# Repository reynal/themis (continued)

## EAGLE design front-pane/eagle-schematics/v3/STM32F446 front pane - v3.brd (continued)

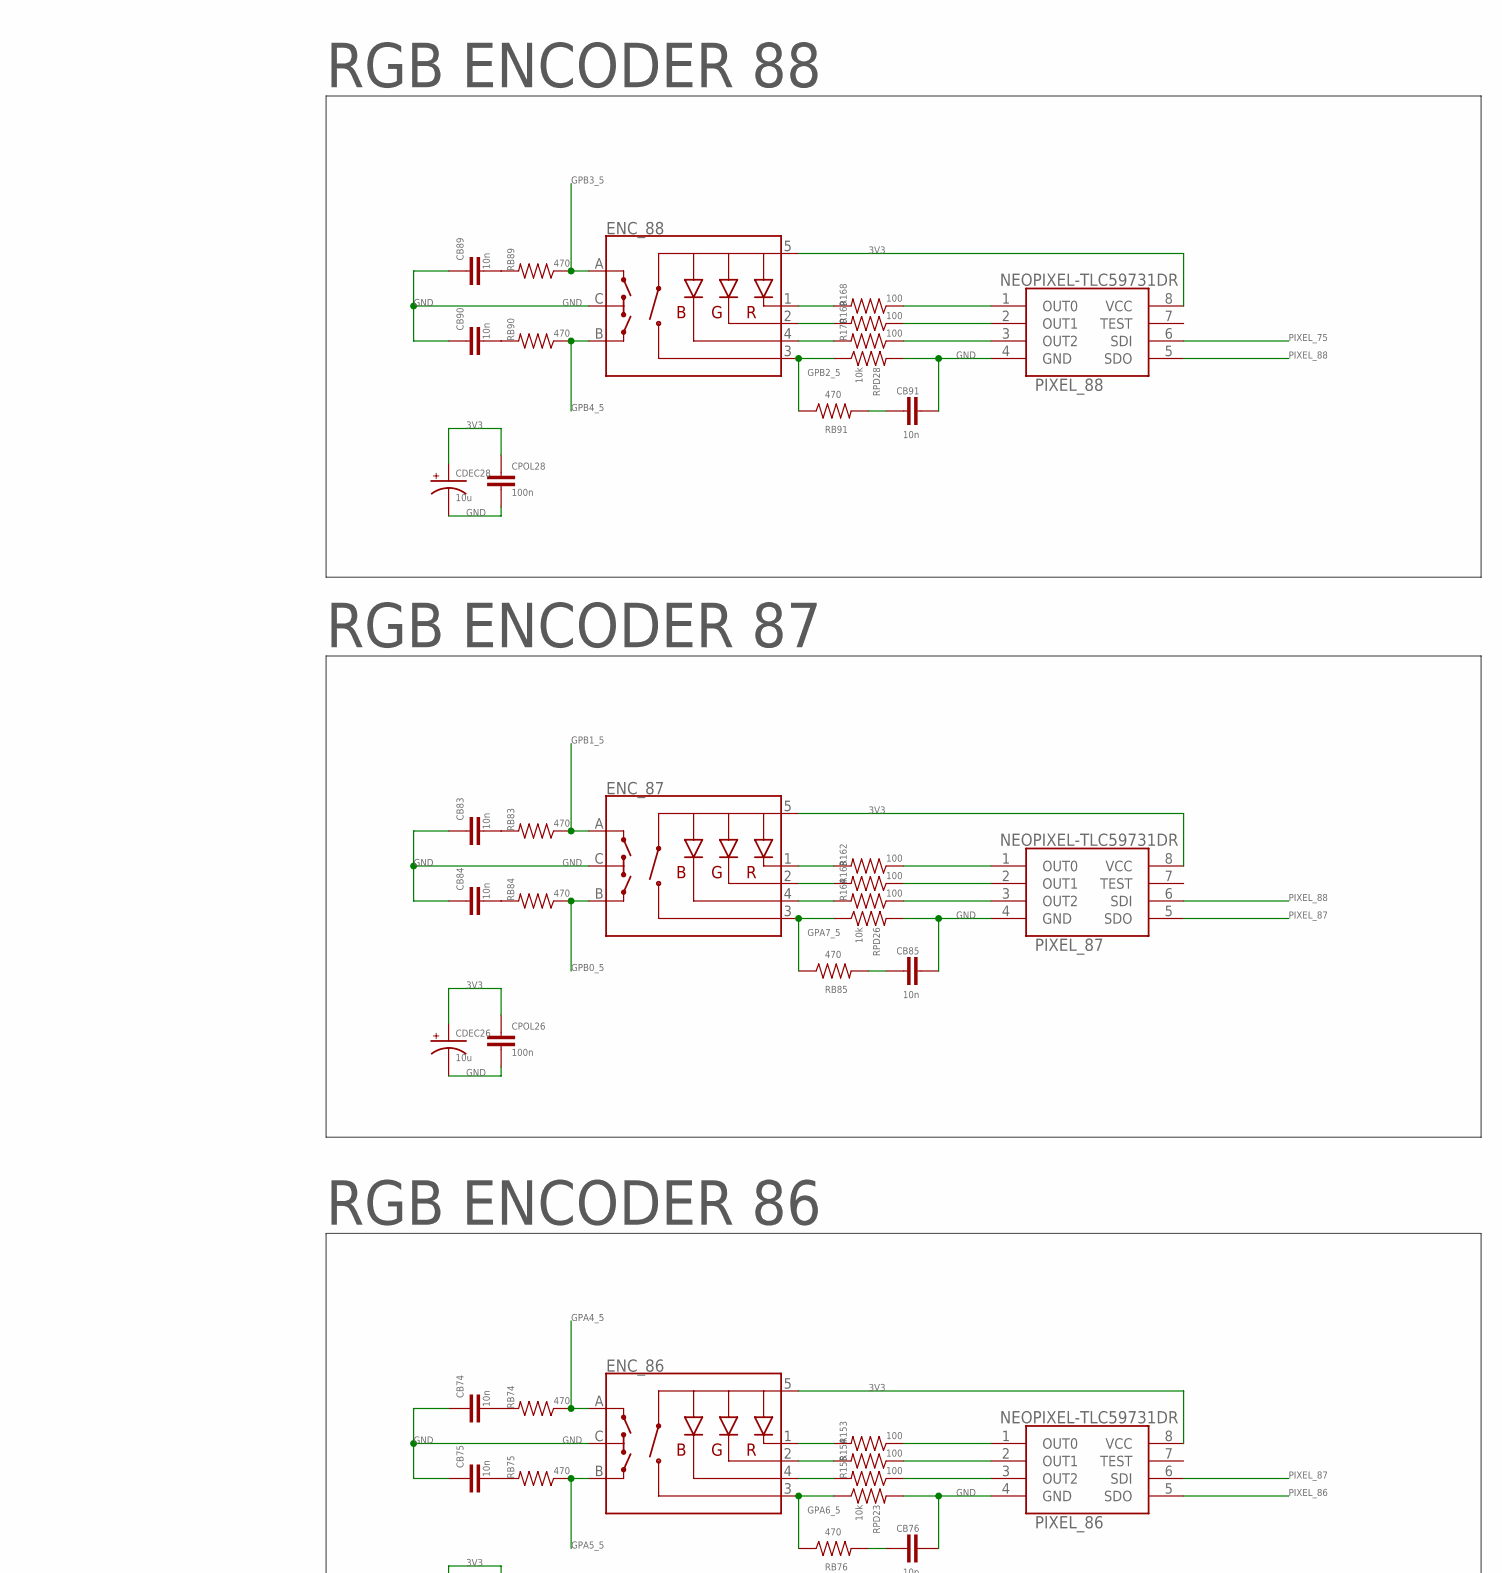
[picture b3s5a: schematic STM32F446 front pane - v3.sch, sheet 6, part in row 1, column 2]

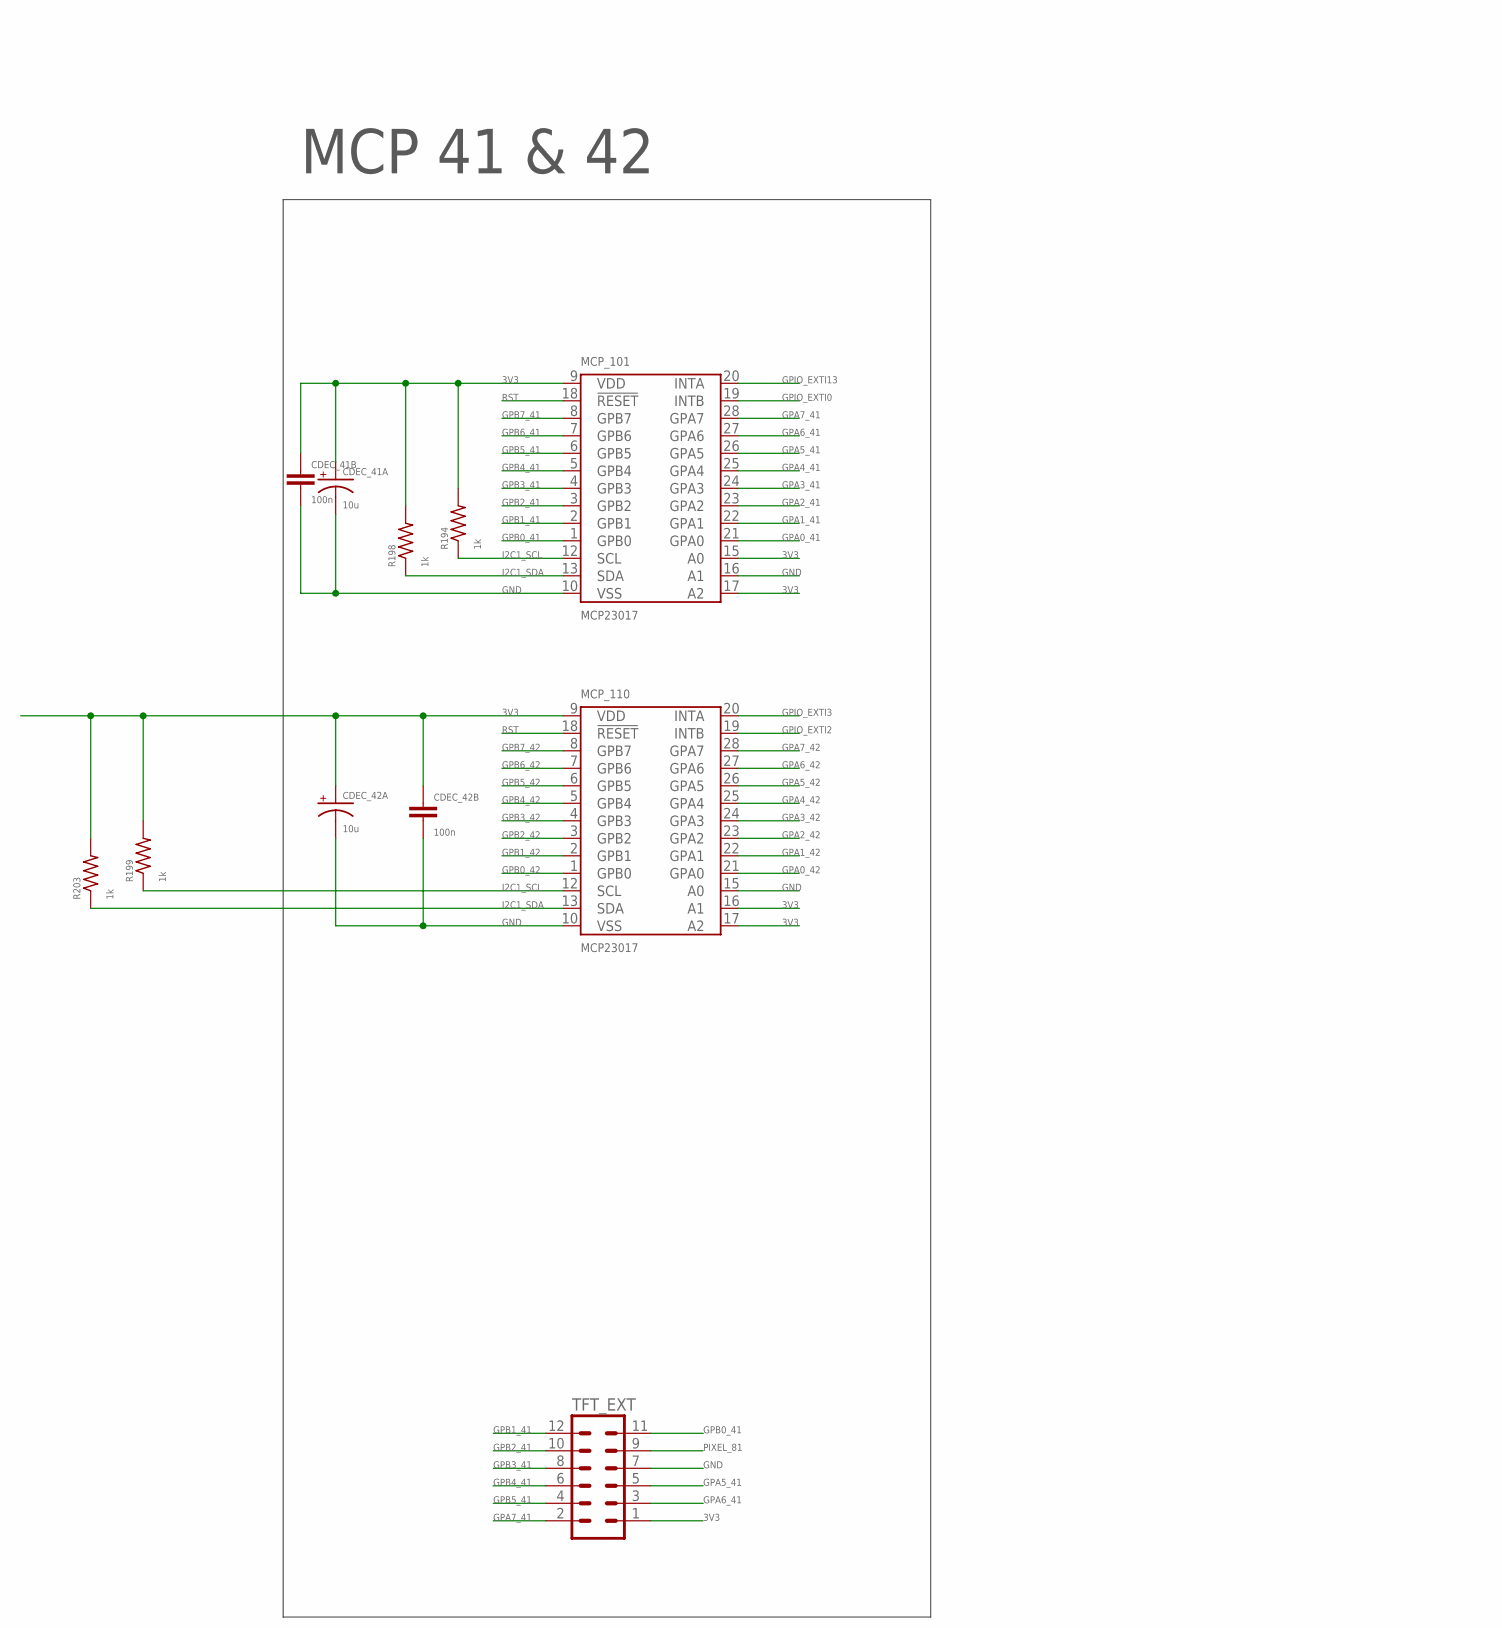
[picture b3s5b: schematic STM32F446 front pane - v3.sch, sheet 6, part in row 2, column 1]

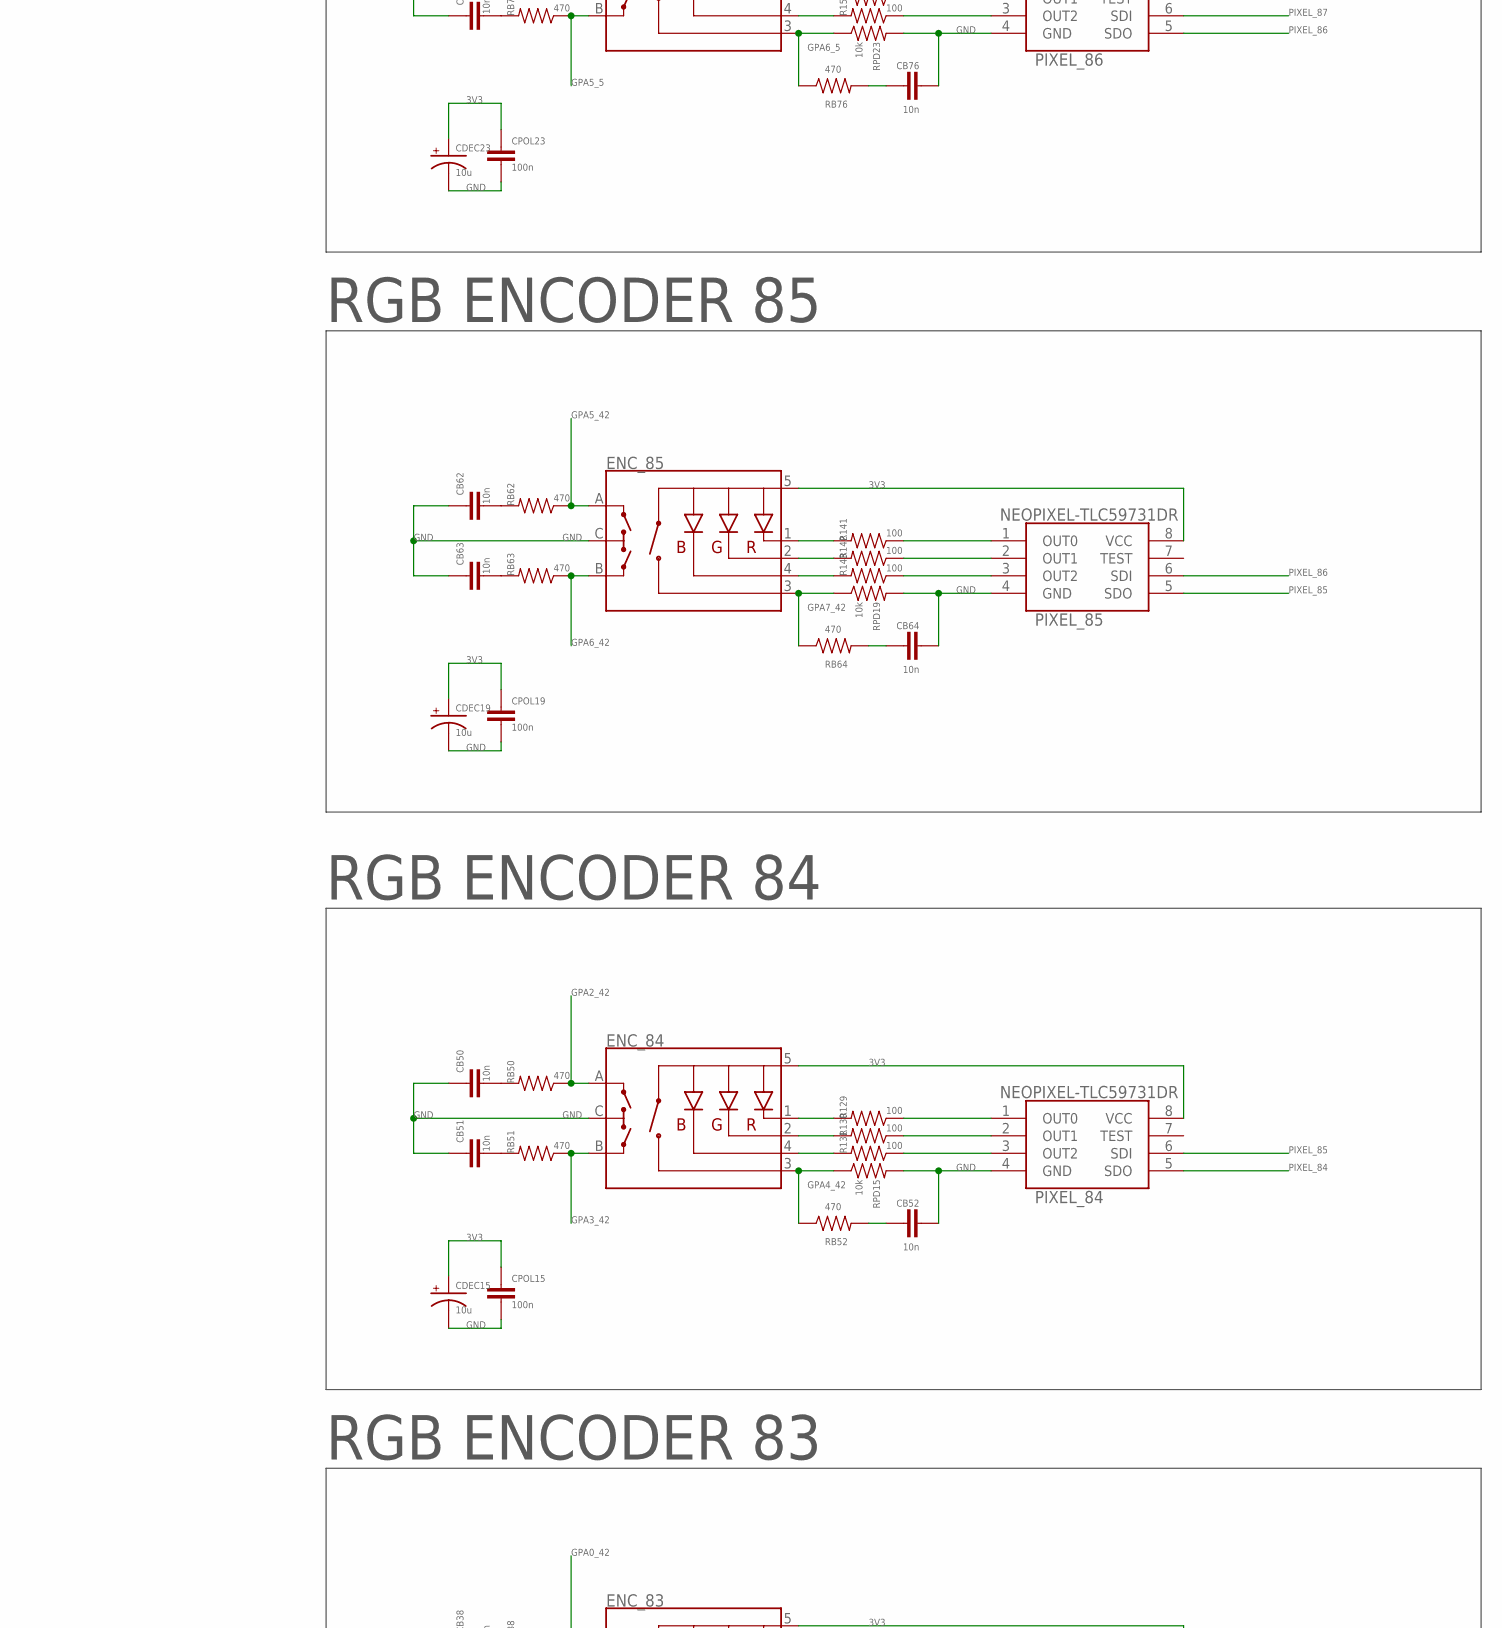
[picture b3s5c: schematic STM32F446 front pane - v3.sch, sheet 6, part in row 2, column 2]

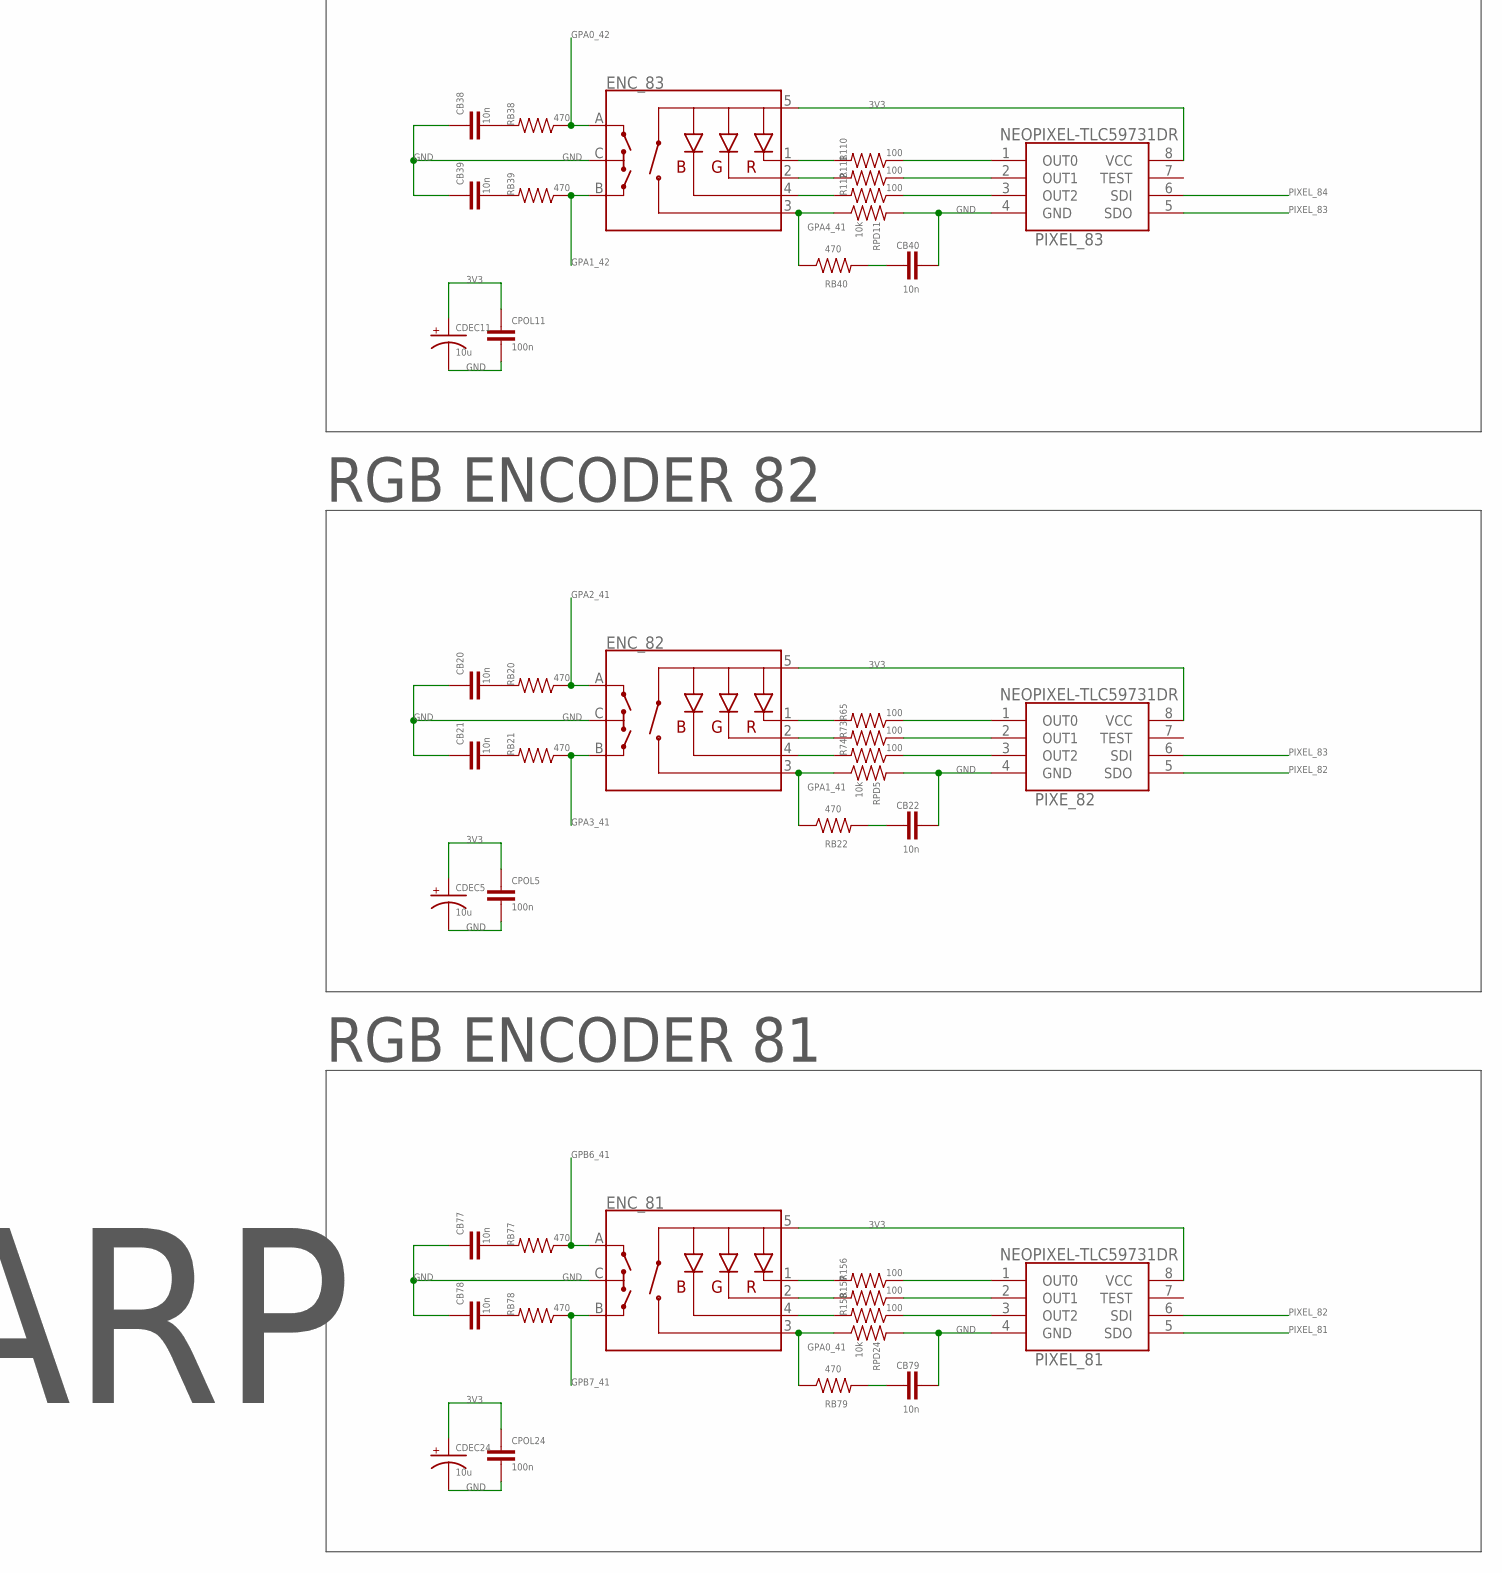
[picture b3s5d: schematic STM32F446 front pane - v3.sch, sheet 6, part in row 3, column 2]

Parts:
CB20, CB21, CB22, CB38, CB39, CB40, CB50, CB51, CB52, CB62, CB63, CB64, CB74, CB75, CB76, CB77, CB78, CB79, CB83, CB84, CB85, CB89, CB90, CB91: 10n; 0805-CAP
CDEC5, CDEC11, CDEC15, CDEC19, CDEC23, CDEC24, CDEC26, CDEC28: 10u; CPOL2917
CDEC_41A, CDEC_42A: 10u; CPOL2917
CDEC_41B, CDEC_42B: 100n; 0805-CAP
CPOL5, CPOL11, CPOL15, CPOL19, CPOL23, CPOL24, CPOL26, CPOL28: 100n; 0805-CAP
ENC_81, ENC_82, ENC_83, ENC_84, ENC_85, ENC_86, ENC_87, ENC_88: ENCODER-RGB-SWITCH-NO_NUT; ENCODER_LED_3
MCP_101, MCP_110: MCP23017; SOIC-28
PIXEL_81, PIXEL_83, PIXEL_84, PIXEL_85, PIXEL_86, PIXEL_87, PIXEL_88: NEOPIXEL-TLC59731DR; SOIC127P600X175-8N
PIXE_82: NEOPIXEL-TLC59731DR; SOIC127P600X175-8N
R65, R73, R74, R110, R111, R112, R129, R130, R131, R141, R142, R143, R153, R154, R155, R156, R157, R158, R162, R163, R164, R168, R169, R170: 100; 1206
R194, R198, R199, R203: 1k; R0805
RB20, RB21, RB22, RB38, RB39, RB40, RB50, RB51, RB52, RB62, RB63, RB64, RB74, RB75, RB76, RB77, RB78, RB79, RB83, RB84, RB85, RB89, RB90, RB91: 470; 1206
RPD5, RPD11, RPD15, RPD19, RPD23, RPD24, RPD26, RPD28: 10k; 1206
TFT_EXT: MA06-2

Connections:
3V3: CDEC5.+, CDEC11.+, CDEC15.+, CDEC19.+, CDEC23.+, CDEC24.+, CDEC26.+, CDEC28.+, CDEC_41A.+, CDEC_41B.1, CDEC_42A.+, CDEC_42B.1, CPOL5.1, CPOL11.1, CPOL15.1, CPOL19.1, CPOL23.1, CPOL24.1, CPOL26.1, CPOL28.1, ENC_81.5 (+), ENC_82.5 (+), ENC_83.5 (+), ENC_84.5 (+), ENC_85.5 (+), ENC_86.5 (+), ENC_87.5 (+), ENC_88.5 (+), MCP_101.9 (VDD), MCP_101.15 (A0), MCP_101.17 (A2), MCP_110.9 (VDD), MCP_110.16 (A1), MCP_110.17 (A2), PIXEL_81.8 (VCC), PIXEL_83.8 (VCC), PIXEL_84.8 (VCC), PIXEL_85.8 (VCC), PIXEL_86.8 (VCC), PIXEL_87.8 (VCC), PIXEL_88.8 (VCC), PIXE_82.8 (VCC), R194.2, R198.2, R199.2, R203.2, TFT_EXT.1; also elsewhere on the board
GND: CB20.1, CB21.1, CB22.2, CB38.1, CB39.1, CB40.2, CB50.1, CB51.1, CB52.2, CB62.1, CB63.1, CB64.2, CB74.1, CB75.1, CB76.2, CB77.1, CB78.1, CB79.2, CB83.1, CB84.1, CB85.2, CB89.1, CB90.1, CB91.2, CDEC5.-, CDEC11.-, CDEC15.-, CDEC19.-, CDEC23.-, CDEC24.-, CDEC26.-, CDEC28.-, CDEC_41A.-, CDEC_41B.2, CDEC_42A.-, CDEC_42B.2, CPOL5.2, CPOL11.2, CPOL15.2, CPOL19.2, CPOL23.2, CPOL24.2, CPOL26.2, CPOL28.2, ENC_81.C, ENC_82.C, ENC_83.C, ENC_84.C, ENC_85.C, ENC_86.C, ENC_87.C, ENC_88.C, MCP_101.10 (VSS), MCP_101.16 (A1), MCP_110.10 (VSS), MCP_110.15 (A0), PIXEL_81.4 (GND), PIXEL_83.4 (GND), PIXEL_84.4 (GND), PIXEL_85.4 (GND), PIXEL_86.4 (GND), PIXEL_87.4 (GND), PIXEL_88.4 (GND), PIXE_82.4 (GND), RPD5.2, RPD11.2, RPD15.2, RPD19.2, RPD23.2, RPD24.2, RPD26.2, RPD28.2, TFT_EXT.7; also elsewhere on the board
GPA0_41: ENC_81.3 (SW), MCP_101.21 (GPA0), RB79.1, RPD24.1
GPA0_42: ENC_83.A, MCP_110.21 (GPA0), RB38.1
GPA1_41: ENC_82.3 (SW), MCP_101.22 (GPA1), RB22.1, RPD5.1
GPA1_42: ENC_83.B, MCP_110.22 (GPA1), RB39.1
GPA2_41: ENC_82.A, MCP_101.23 (GPA2), RB20.1
GPA2_42: ENC_84.A, MCP_110.23 (GPA2), RB50.1
GPA3_41: ENC_82.B, MCP_101.24 (GPA3), RB21.1
GPA3_42: ENC_84.B, MCP_110.24 (GPA3), RB51.1
GPA4_5: ENC_86.A, RB74.1; also elsewhere on the board
GPA4_41: ENC_83.3 (SW), MCP_101.25 (GPA4), RB40.1, RPD11.1
GPA4_42: ENC_84.3 (SW), MCP_110.25 (GPA4), RB52.1, RPD15.1
GPA5_5: ENC_86.B, RB75.1; also elsewhere on the board
GPA5_41: MCP_101.26 (GPA5), TFT_EXT.5
GPA5_42: ENC_85.A, MCP_110.26 (GPA5), RB62.1
GPA6_5: ENC_86.3 (SW), RB76.1, RPD23.1; also elsewhere on the board
GPA6_41: MCP_101.27 (GPA6), TFT_EXT.3
GPA6_42: ENC_85.B, MCP_110.27 (GPA6), RB63.1
GPA7_5: ENC_87.3 (SW), RB85.1, RPD26.1; also elsewhere on the board
GPA7_41: MCP_101.28 (GPA7), TFT_EXT.2
GPA7_42: ENC_85.3 (SW), MCP_110.28 (GPA7), RB64.1, RPD19.1
GPB0_5: ENC_87.B, RB84.1; also elsewhere on the board
GPB0_41: MCP_101.1 (GPB0), TFT_EXT.11
GPB0_42: MCP_110.1 (GPB0); also elsewhere on the board
GPB1_5: ENC_87.A, RB83.1; also elsewhere on the board
GPB1_41: MCP_101.2 (GPB1), TFT_EXT.12
GPB1_42: MCP_110.2 (GPB1); also elsewhere on the board
GPB2_5: ENC_88.3 (SW), RB91.1, RPD28.1; also elsewhere on the board
GPB2_41: MCP_101.3 (GPB2), TFT_EXT.10
GPB2_42: MCP_110.3 (GPB2); also elsewhere on the board
GPB3_5: ENC_88.A, RB89.1; also elsewhere on the board
GPB3_41: MCP_101.4 (GPB3), TFT_EXT.8
GPB3_42: MCP_110.4 (GPB3); also elsewhere on the board
GPB4_5: ENC_88.B, RB90.1; also elsewhere on the board
GPB4_41: MCP_101.5 (GPB4), TFT_EXT.6
GPB4_42: MCP_110.5 (GPB4); also elsewhere on the board
GPB5_41: MCP_101.6 (GPB5), TFT_EXT.4
GPB5_42: MCP_110.6 (GPB5); also elsewhere on the board
GPB6_41: ENC_81.A, MCP_101.7 (GPB6), RB77.1
GPB6_42: MCP_110.7 (GPB6); also elsewhere on the board
GPB7_41: ENC_81.B, MCP_101.8 (GPB7), RB78.1
GPB7_42: MCP_110.8 (GPB7); also elsewhere on the board
GPIO_EXTI0: MCP_101.19 (INTB); also elsewhere on the board
GPIO_EXTI2: MCP_110.19 (INTB); also elsewhere on the board
GPIO_EXTI3: MCP_110.20 (INTA); also elsewhere on the board
GPIO_EXTI13: MCP_101.20 (INTA); also elsewhere on the board
I2C1_SCL: MCP_101.12 (SCL), MCP_110.12 (SCL), R194.1, R199.1; also elsewhere on the board
I2C1_SDA: MCP_101.13 (SDA), MCP_110.13 (SDA), R198.1, R203.1; also elsewhere on the board
unnamed: ENC_82.1 (-R), R65.2
unnamed: ENC_82.2 (-G), R73.2
unnamed: ENC_82.4 (-B), R74.2
unnamed: PIXE_82.1 (OUT0), R65.1
unnamed: PIXE_82.2 (OUT1), R73.1
unnamed: PIXE_82.3 (OUT2), R74.1
unnamed: CB20.2, RB20.2
unnamed: CB21.2, RB21.2
unnamed: CB22.1, RB22.2
unnamed: ENC_83.1 (-R), R110.2
unnamed: ENC_83.2 (-G), R111.2
unnamed: ENC_83.4 (-B), R112.2
unnamed: PIXEL_83.1 (OUT0), R110.1
unnamed: PIXEL_83.2 (OUT1), R111.1
unnamed: PIXEL_83.3 (OUT2), R112.1
unnamed: CB38.2, RB38.2
unnamed: CB39.2, RB39.2
unnamed: CB40.1, RB40.2
unnamed: ENC_84.1 (-R), R129.2
unnamed: ENC_84.2 (-G), R130.2
unnamed: ENC_84.4 (-B), R131.2
unnamed: PIXEL_84.1 (OUT0), R129.1
unnamed: PIXEL_84.2 (OUT1), R130.1
unnamed: PIXEL_84.3 (OUT2), R131.1
unnamed: CB50.2, RB50.2
unnamed: CB51.2, RB51.2
unnamed: CB52.1, RB52.2
unnamed: ENC_85.1 (-R), R141.2
unnamed: ENC_85.2 (-G), R142.2
unnamed: ENC_85.4 (-B), R143.2
unnamed: PIXEL_85.1 (OUT0), R141.1
unnamed: PIXEL_85.2 (OUT1), R142.1
unnamed: PIXEL_85.3 (OUT2), R143.1
unnamed: CB62.2, RB62.2
unnamed: CB63.2, RB63.2
unnamed: CB64.1, RB64.2
unnamed: ENC_86.1 (-R), R153.2
unnamed: ENC_86.2 (-G), R154.2
unnamed: ENC_86.4 (-B), R155.2
unnamed: PIXEL_86.1 (OUT0), R153.1
unnamed: PIXEL_86.2 (OUT1), R154.1
unnamed: PIXEL_86.3 (OUT2), R155.1
unnamed: CB74.2, RB74.2
unnamed: CB75.2, RB75.2
unnamed: CB76.1, RB76.2
unnamed: ENC_81.1 (-R), R156.2
unnamed: ENC_81.2 (-G), R157.2
unnamed: ENC_81.4 (-B), R158.2
unnamed: PIXEL_81.1 (OUT0), R156.1
unnamed: PIXEL_81.2 (OUT1), R157.1
unnamed: PIXEL_81.3 (OUT2), R158.1
unnamed: CB77.2, RB77.2
unnamed: CB78.2, RB78.2
unnamed: CB79.1, RB79.2
unnamed: ENC_87.1 (-R), R162.2
unnamed: ENC_87.2 (-G), R163.2
unnamed: ENC_87.4 (-B), R164.2
unnamed: PIXEL_87.1 (OUT0), R162.1
unnamed: PIXEL_87.2 (OUT1), R163.1
unnamed: PIXEL_87.3 (OUT2), R164.1
unnamed: CB83.2, RB83.2
unnamed: CB84.2, RB84.2
unnamed: CB85.1, RB85.2
unnamed: ENC_88.1 (-R), R168.2
unnamed: ENC_88.2 (-G), R169.2
unnamed: ENC_88.4 (-B), R170.2
unnamed: PIXEL_88.1 (OUT0), R168.1
unnamed: PIXEL_88.2 (OUT1), R169.1
unnamed: PIXEL_88.3 (OUT2), R170.1
unnamed: CB89.2, RB89.2
unnamed: CB90.2, RB90.2
unnamed: CB91.1, RB91.2
PIXEL_75: PIXEL_88.6 (SDI); also elsewhere on the board
PIXEL_81: PIXEL_81.5 (SDO), TFT_EXT.9
PIXEL_82: PIXEL_81.6 (SDI), PIXE_82.5 (SDO)
PIXEL_83: PIXEL_83.5 (SDO), PIXE_82.6 (SDI)
PIXEL_84: PIXEL_83.6 (SDI), PIXEL_84.5 (SDO)
PIXEL_85: PIXEL_84.6 (SDI), PIXEL_85.5 (SDO)
PIXEL_86: PIXEL_85.6 (SDI), PIXEL_86.5 (SDO)
PIXEL_87: PIXEL_86.6 (SDI), PIXEL_87.5 (SDO)
PIXEL_88: PIXEL_87.6 (SDI), PIXEL_88.5 (SDO)
RST: MCP_101.18 (!RESET), MCP_110.18 (!RESET); also elsewhere on the board

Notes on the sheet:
ARP
RGB ENCODER 81
RGB ENCODER 82
RGB ENCODER 83
RGB ENCODER 84
RGB ENCODER 85
RGB ENCODER 86
RGB ENCODER 87
RGB ENCODER 88
MCP 41 & 42

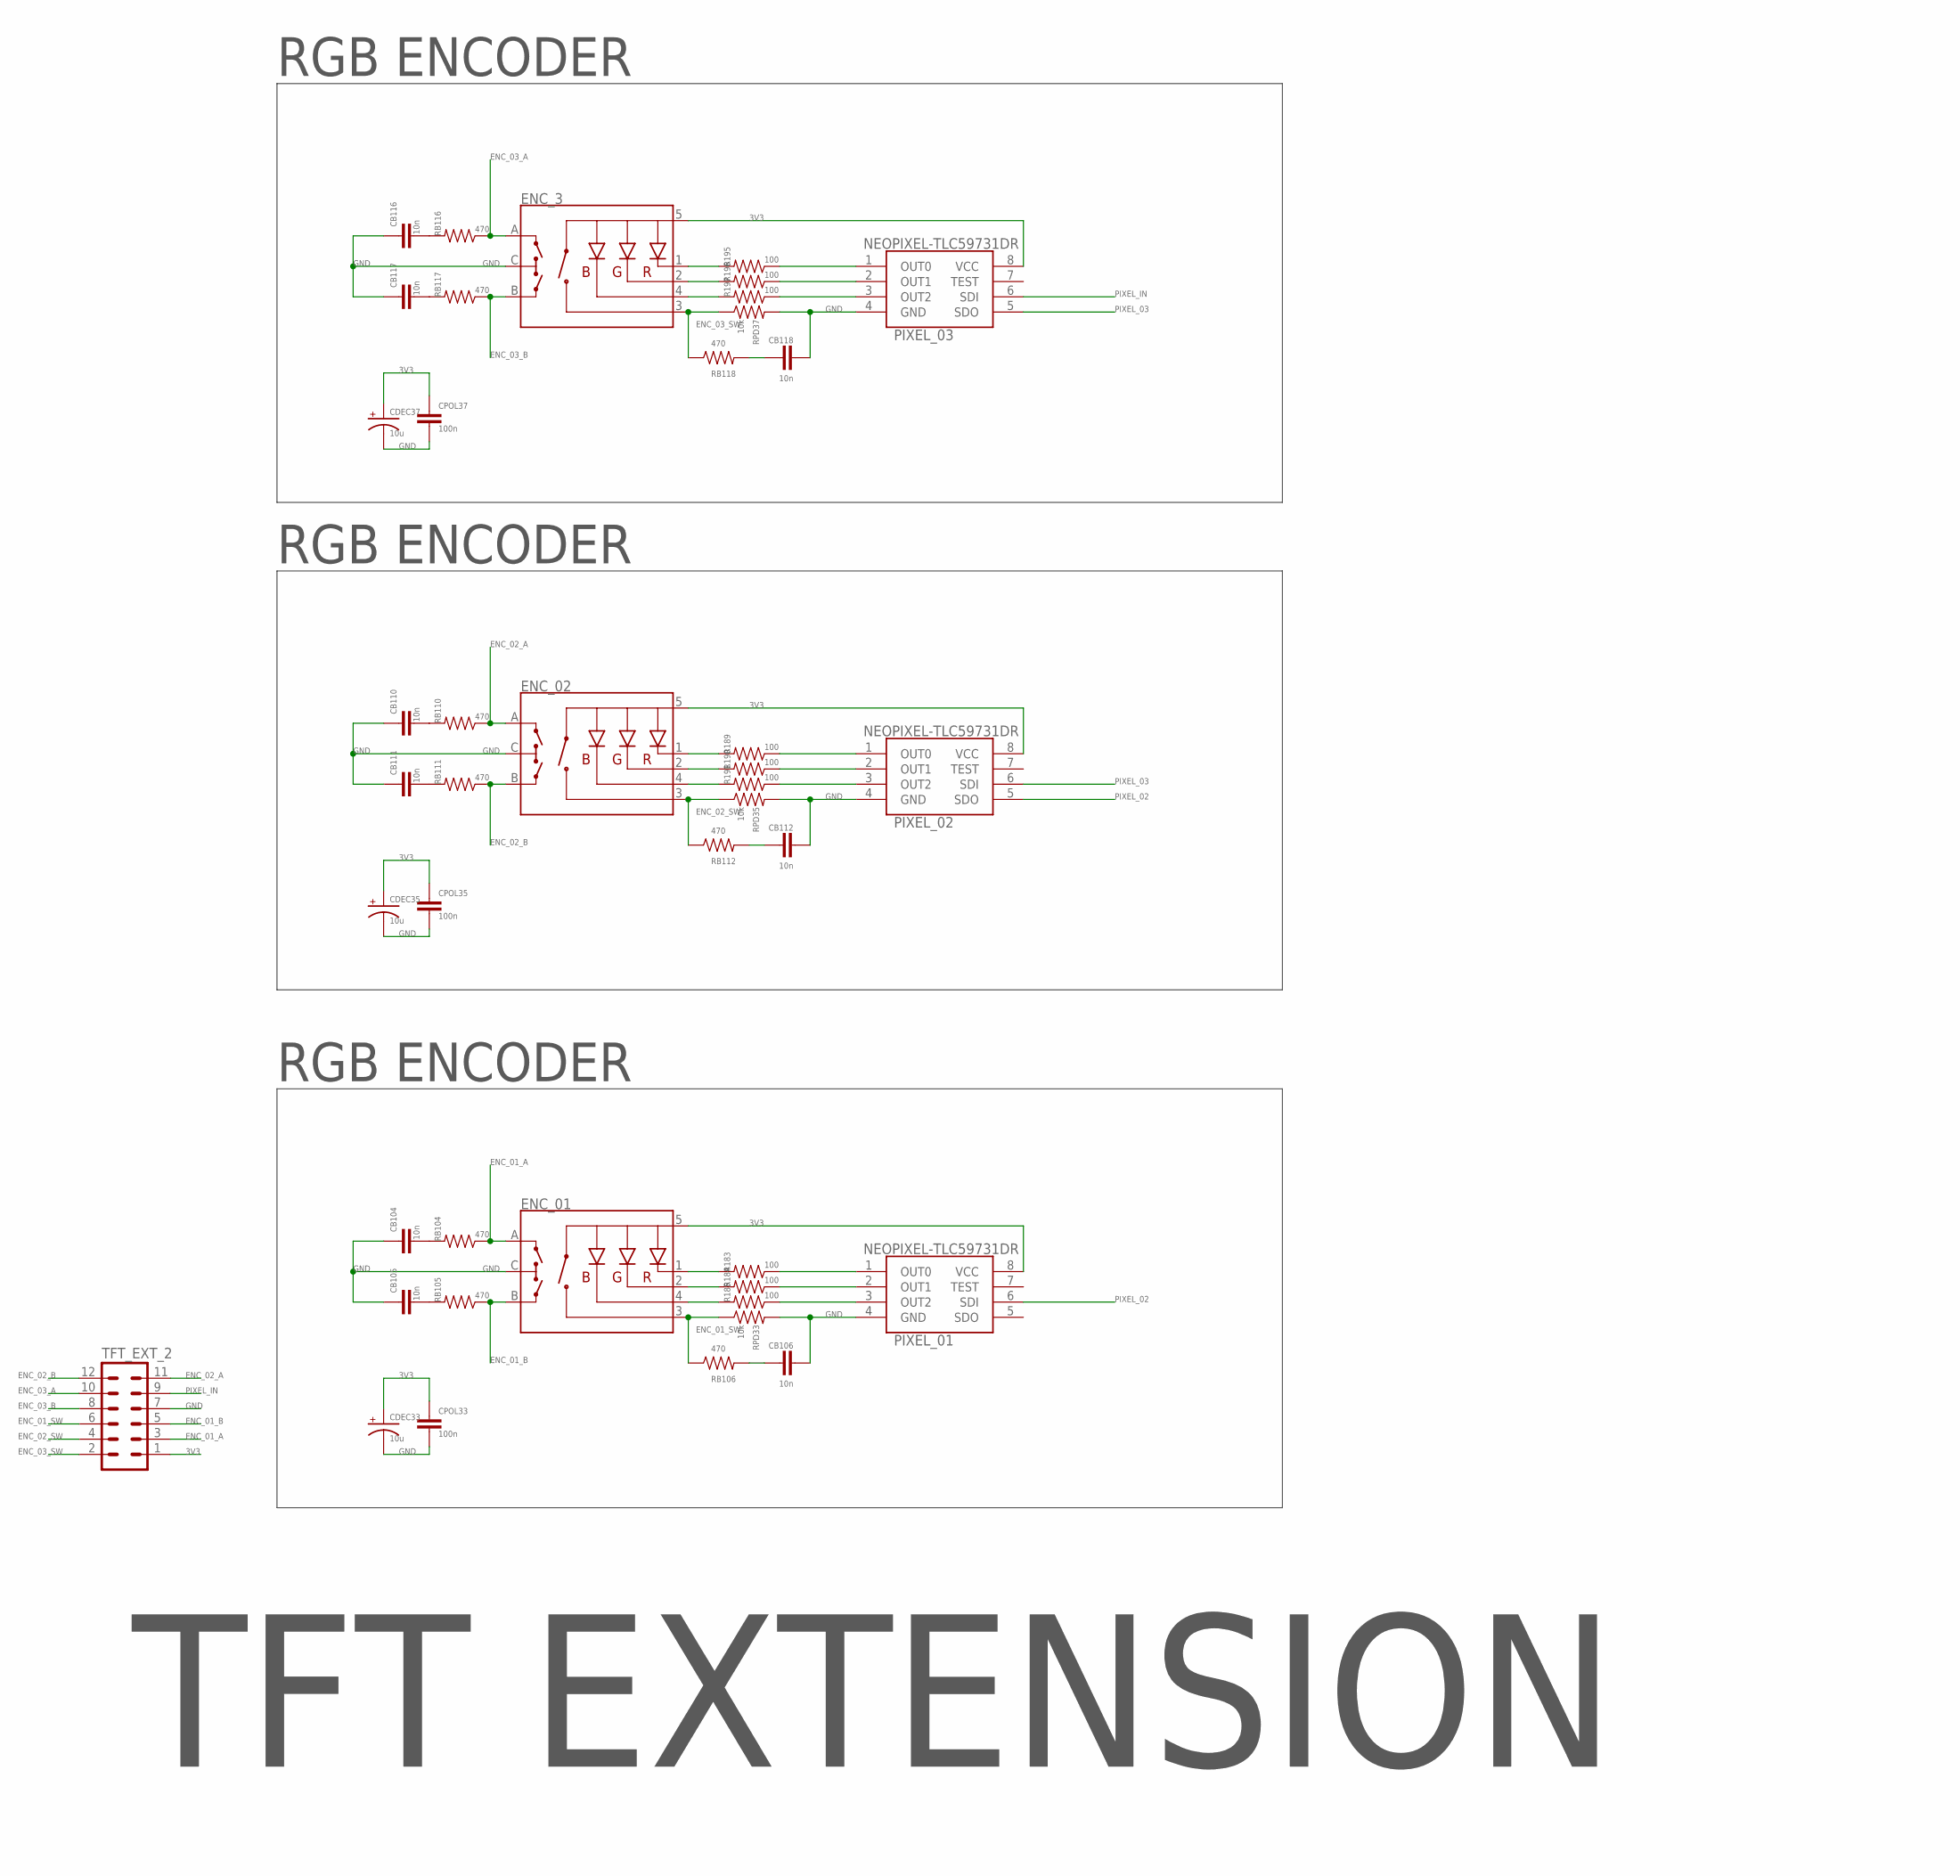
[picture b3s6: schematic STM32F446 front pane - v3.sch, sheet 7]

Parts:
CB104, CB105, CB106, CB110, CB111, CB112, CB116, CB117, CB118: 10n; 0805-CAP
CDEC33, CDEC35, CDEC37: 10u; CPOL2917
CPOL33, CPOL35, CPOL37: 100n; 0805-CAP
ENC_01, ENC_02, ENC_3: ENCODER-RGB-SWITCH-NO_NUT; ENCODER_LED_3
PIXEL_01, PIXEL_02, PIXEL_03: NEOPIXEL-TLC59731DR; SOIC127P600X175-8N
R183, R184, R185, R189, R190, R191, R195, R196, R197: 100; 1206
RB104, RB105, RB106, RB110, RB111, RB112, RB116, RB117, RB118: 470; 1206
RPD33, RPD35, RPD37: 10k; 1206
TFT_EXT_2: MA06-2

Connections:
3V3: CDEC33.+, CDEC35.+, CDEC37.+, CPOL33.1, CPOL35.1, CPOL37.1, ENC_01.5 (+), ENC_02.5 (+), ENC_3.5 (+), PIXEL_01.8 (VCC), PIXEL_02.8 (VCC), PIXEL_03.8 (VCC), TFT_EXT_2.1; also elsewhere on the board
ENC_01_A: ENC_01.A, RB104.1, TFT_EXT_2.3
ENC_01_B: ENC_01.B, RB105.1, TFT_EXT_2.5
ENC_01_SW: ENC_01.3 (SW), RB106.1, RPD33.1, TFT_EXT_2.6
ENC_02_A: ENC_02.A, RB110.1, TFT_EXT_2.11
ENC_02_B: ENC_02.B, RB111.1, TFT_EXT_2.12
ENC_02_SW: ENC_02.3 (SW), RB112.1, RPD35.1, TFT_EXT_2.4
ENC_03_A: ENC_3.A, RB116.1, TFT_EXT_2.10
ENC_03_B: ENC_3.B, RB117.1, TFT_EXT_2.8
ENC_03_SW: ENC_3.3 (SW), RB118.1, RPD37.1, TFT_EXT_2.2
GND: CB104.1, CB105.1, CB106.2, CB110.1, CB111.1, CB112.2, CB116.1, CB117.1, CB118.2, CDEC33.-, CDEC35.-, CDEC37.-, CPOL33.2, CPOL35.2, CPOL37.2, ENC_01.C, ENC_02.C, ENC_3.C, PIXEL_01.4 (GND), PIXEL_02.4 (GND), PIXEL_03.4 (GND), RPD33.2, RPD35.2, RPD37.2, TFT_EXT_2.7; also elsewhere on the board
unnamed: ENC_01.1 (-R), R183.2
unnamed: ENC_01.2 (-G), R184.2
unnamed: ENC_01.4 (-B), R185.2
unnamed: PIXEL_01.1 (OUT0), R183.1
unnamed: PIXEL_01.2 (OUT1), R184.1
unnamed: PIXEL_01.3 (OUT2), R185.1
unnamed: CB104.2, RB104.2
unnamed: CB105.2, RB105.2
unnamed: CB106.1, RB106.2
unnamed: ENC_02.1 (-R), R189.2
unnamed: ENC_02.2 (-G), R190.2
unnamed: ENC_02.4 (-B), R191.2
unnamed: PIXEL_02.1 (OUT0), R189.1
unnamed: PIXEL_02.2 (OUT1), R190.1
unnamed: PIXEL_02.3 (OUT2), R191.1
unnamed: CB110.2, RB110.2
unnamed: CB111.2, RB111.2
unnamed: CB112.1, RB112.2
unnamed: ENC_3.1 (-R), R195.2
unnamed: ENC_3.2 (-G), R196.2
unnamed: ENC_3.4 (-B), R197.2
unnamed: PIXEL_03.1 (OUT0), R195.1
unnamed: PIXEL_03.2 (OUT1), R196.1
unnamed: PIXEL_03.3 (OUT2), R197.1
unnamed: CB116.2, RB116.2
unnamed: CB117.2, RB117.2
unnamed: CB118.1, RB118.2
PIXEL_02: PIXEL_01.6 (SDI), PIXEL_02.5 (SDO)
PIXEL_03: PIXEL_02.6 (SDI), PIXEL_03.5 (SDO)
PIXEL_IN: PIXEL_03.6 (SDI), TFT_EXT_2.9

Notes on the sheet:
TFT EXTENSION
RGB ENCODER

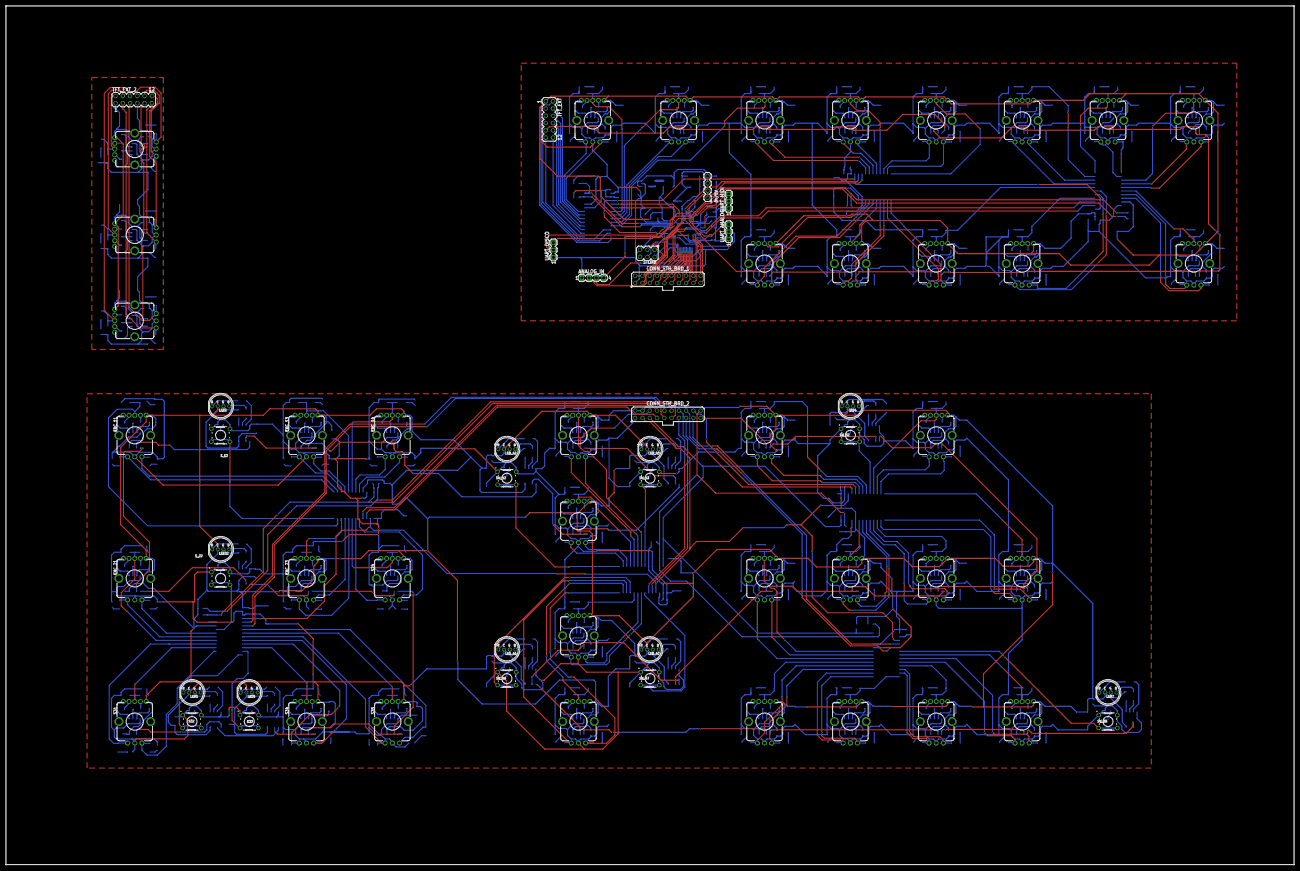
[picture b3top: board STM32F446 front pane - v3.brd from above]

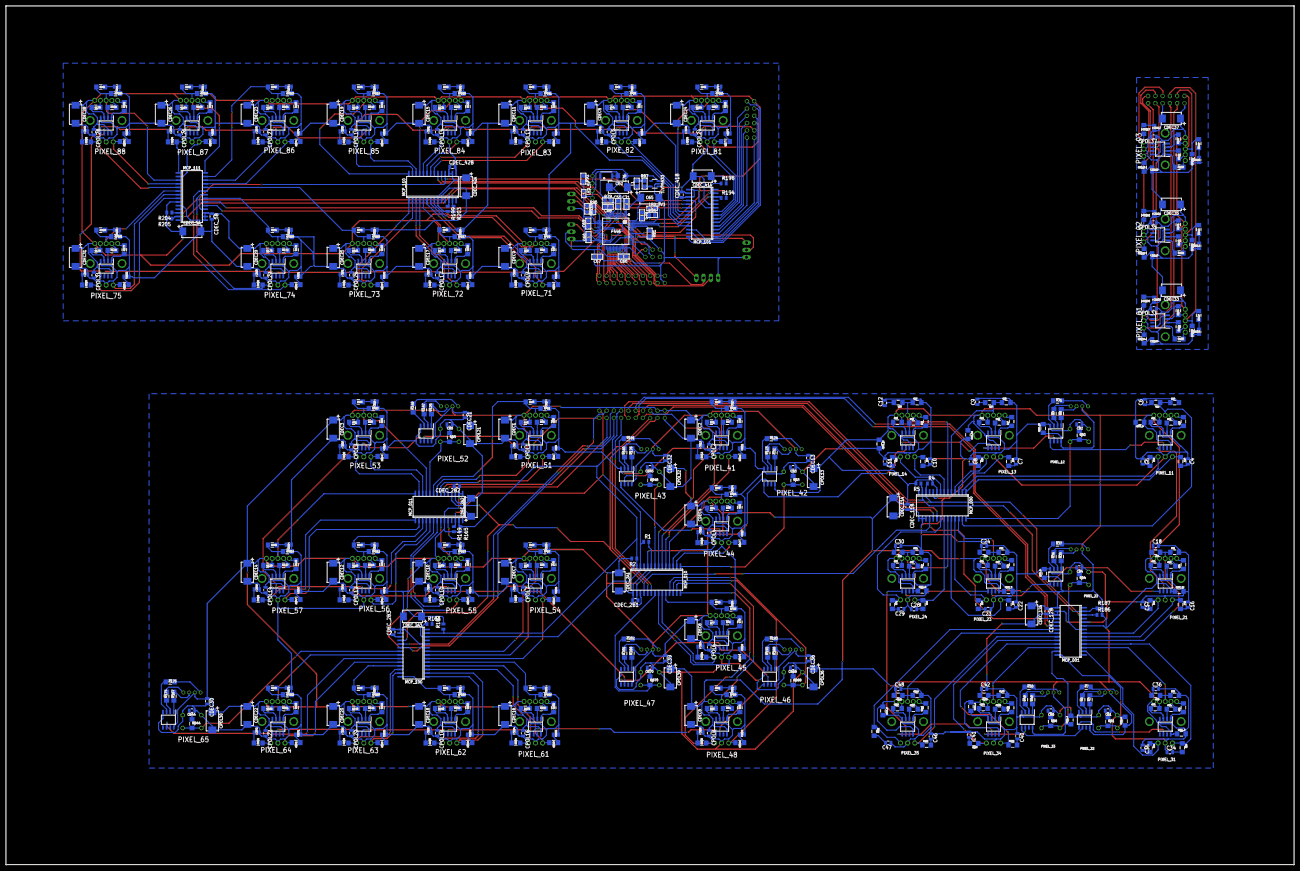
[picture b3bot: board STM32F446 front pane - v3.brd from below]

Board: 2 copper layers, 450.0 x 300.0 mm, 707 parts (638 on the bottom side), 663 nets.
